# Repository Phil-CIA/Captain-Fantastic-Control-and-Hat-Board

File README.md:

# Captain Fantastic Control and HAT Board

Focused hardware repo for the **Captain Fantastic Home Edition** base control board and its companion **HAT board**.

## Scope
Originally, the system was built around two main boards:
- the **matrix board**
- the **control board**

During development, the control section was split into two physical boards:
- the **base control board**
- the **HAT board**

The HAT board is **not** a revision of the control board. It is a companion board that was created when the original control board was split for development work.

> The separate lamp/switch matrix board work lives in the dedicated repo: `Pinball-Sw-Lamp-Matrix-`.

## Repo layout
- `hardware/control-board/` – current base control-board KiCad source for the next redesign pass
- `hardware/control-board/archive/` – older control-board snapshots and backup exports kept for reference
- `hardware/hat-board/` – companion HAT-board KiCad source
- `firmware/control-board/` – clean control-board firmware baseline for this repo
- `docs/` – project status, redesign notes, firmware migration notes, and bring-up checklists

## Current firmware definition draft
- `firmware/control-board/docs/SYSTEM_BEHAVIOR_CONTRACT.md` – working behavior contract for game states, scoring, audio policy, storage budget, diagnostics, and unresolved decisions to lock before code work
- `docs/SYSTEM_BEHAVIOR_CONTRACT.md` – top-level copy of the same contract for quick review/edit from the main docs area
- `docs/SYSTEM_BEHAVIOR_CONTRACT_MATRIX_BOARD.md` – matrix-board companion contract with lockable decisions and iterative question rounds for switch/lamp protocol behavior

## Current status
- New focused repo created on **2026-04-09**
- The current KiCad files uploaded to GitHub for both boards have been merged into this cleaned repo baseline
- A **.96-inch SSD1306-style I2C OLED** has also been added as a troubleshooting display for boot messages and local status during bring-up
- The next PCB change will likely **not** be the last one; the goal is to keep building and developing the hardware while collecting more real-world feedback
- Two redesign blockers are currently tracked:
  1. the **P-channel solenoid-drive section on the base board sees gate-drive conditions above the recommended `Vgs` range when used on the 26 V supply**
  2. the **HAT-board connector did not line up with the base board**, although there is a temporary development workaround

## Next steps
1. build the board for firmware development and, if needed for proof-of-life output checks, feed **both rails from a current-limited 5 V source** rather than the real 26 V supply
2. use `docs/INITIAL_STUFFING_GUIDE.md` and `docs/BENCH_STUFFING_CHECKLIST.md` to decide what to populate now versus later
3. follow the safe bring-up procedure in `docs/FIRST_POWERUP_CHECKLIST.md`
4. proceed with the **single-channel `TPS1H200A-Q1` smart high-side** respin direction using `docs/SOLENOID_DRIVER_SELECTION.md`, `docs/SINGLE_CHANNEL_SOLENOID_LAYOUT.md`, and `docs/SMART_SWITCH_CHANNEL_BLOCK.md` while continuing the clean firmware migration in `firmware/control-board/`

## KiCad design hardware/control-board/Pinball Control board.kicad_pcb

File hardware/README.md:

# Hardware Notes

This folder contains the hardware design files for the Captain Fantastic base control board and its companion HAT board.

## Contents
- `control-board/` – current base control-board KiCad project and related files
- `control-board/archive/` – older control-board snapshots and backup exports kept for reference
- `hat-board/` – companion HAT-board KiCad project

## Guidance
- The HAT board is **not** a revision of the control board; it was created when the original control board was split during development.
- Treat the uploaded KiCad files now stored under `hardware/` as the **authoritative baseline** for the next redesign pass.
- As redesign decisions are made, keep the active source clearly identified and move stale artifacts out of the way.

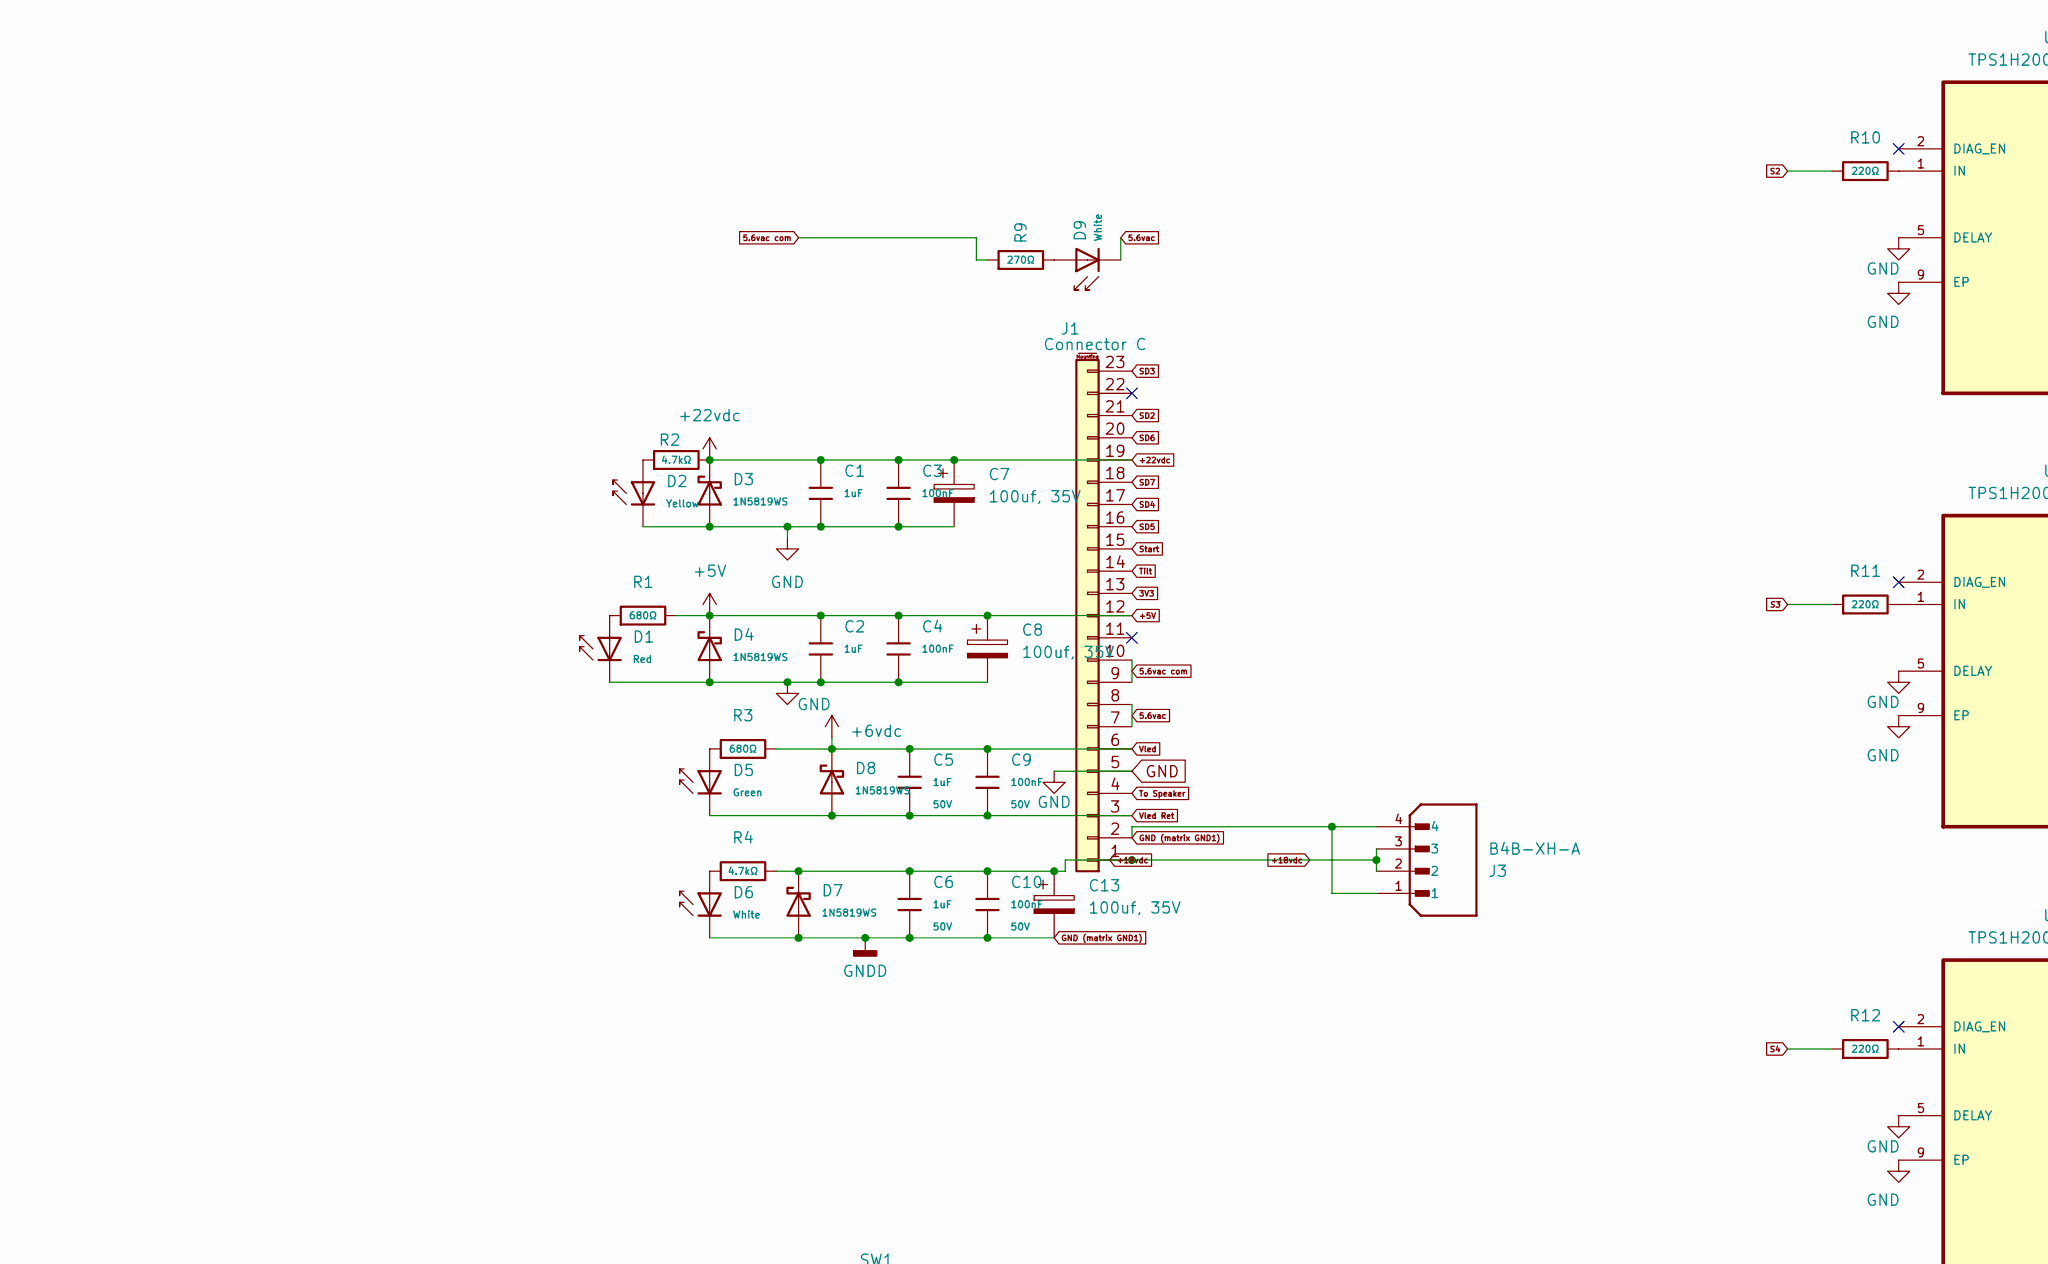
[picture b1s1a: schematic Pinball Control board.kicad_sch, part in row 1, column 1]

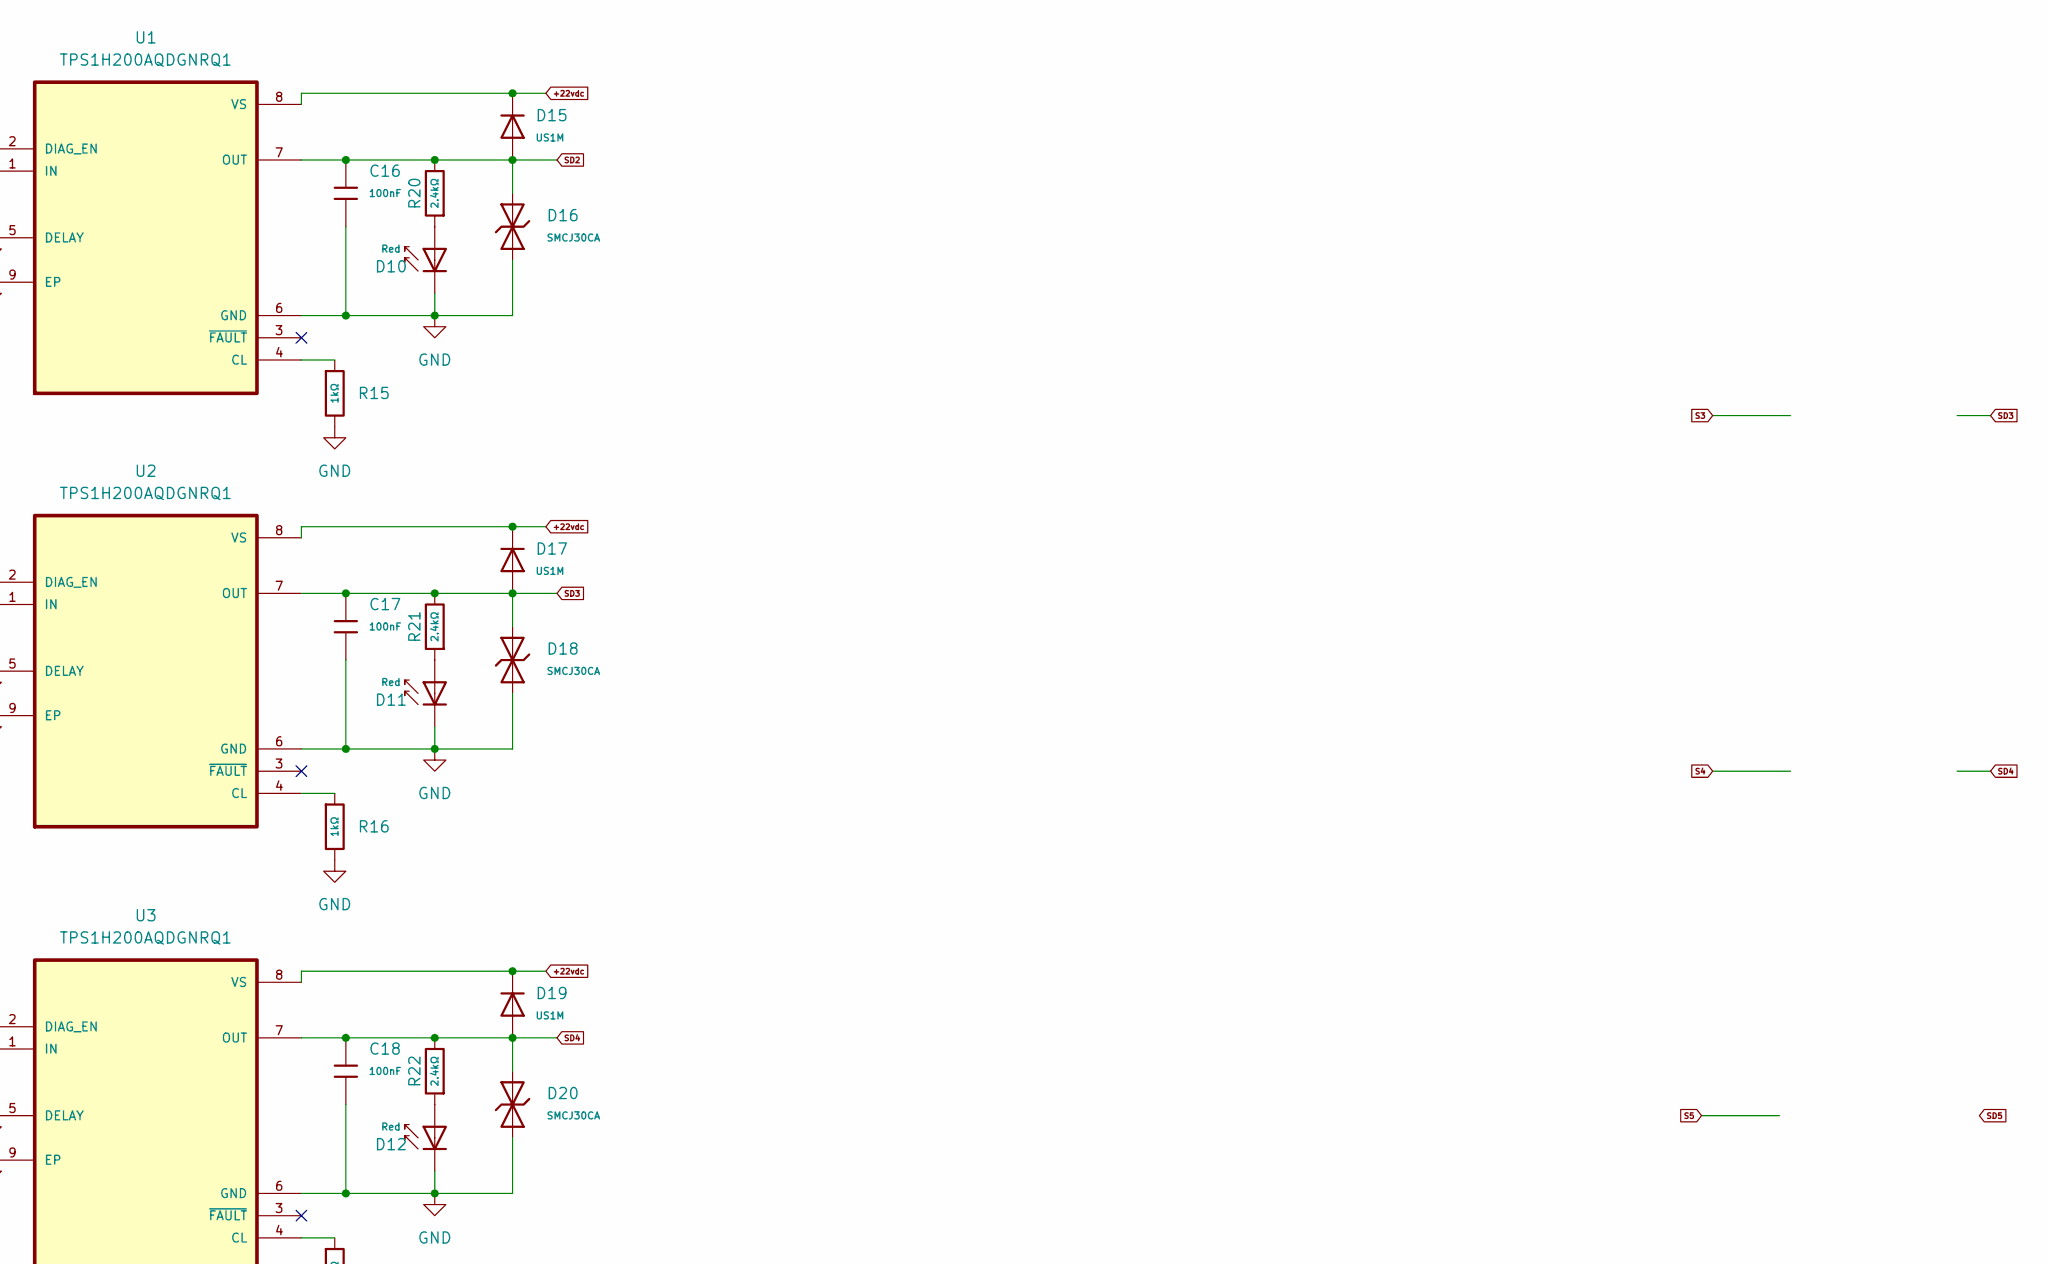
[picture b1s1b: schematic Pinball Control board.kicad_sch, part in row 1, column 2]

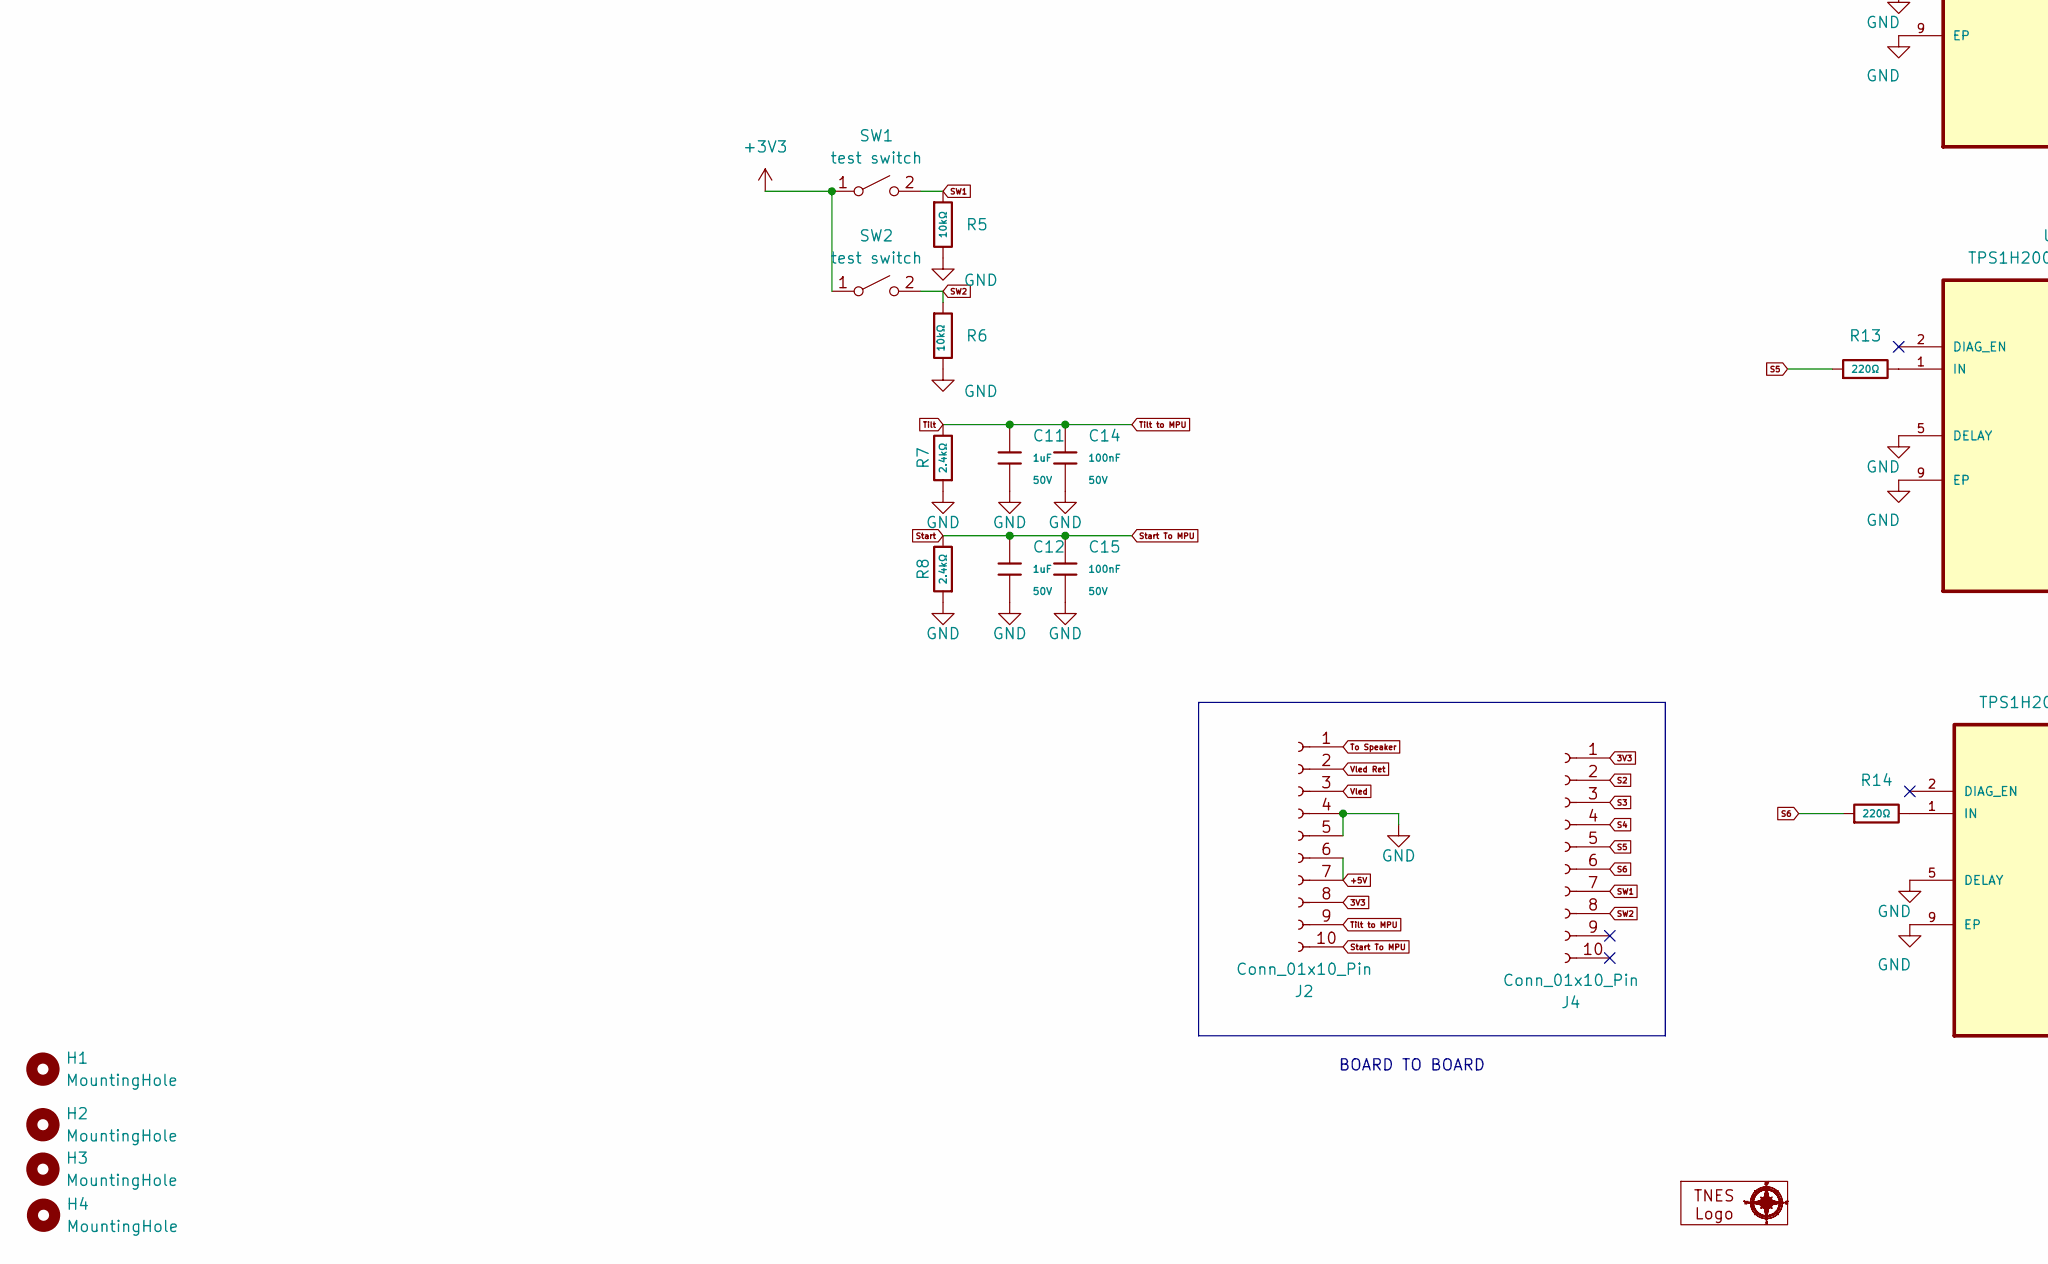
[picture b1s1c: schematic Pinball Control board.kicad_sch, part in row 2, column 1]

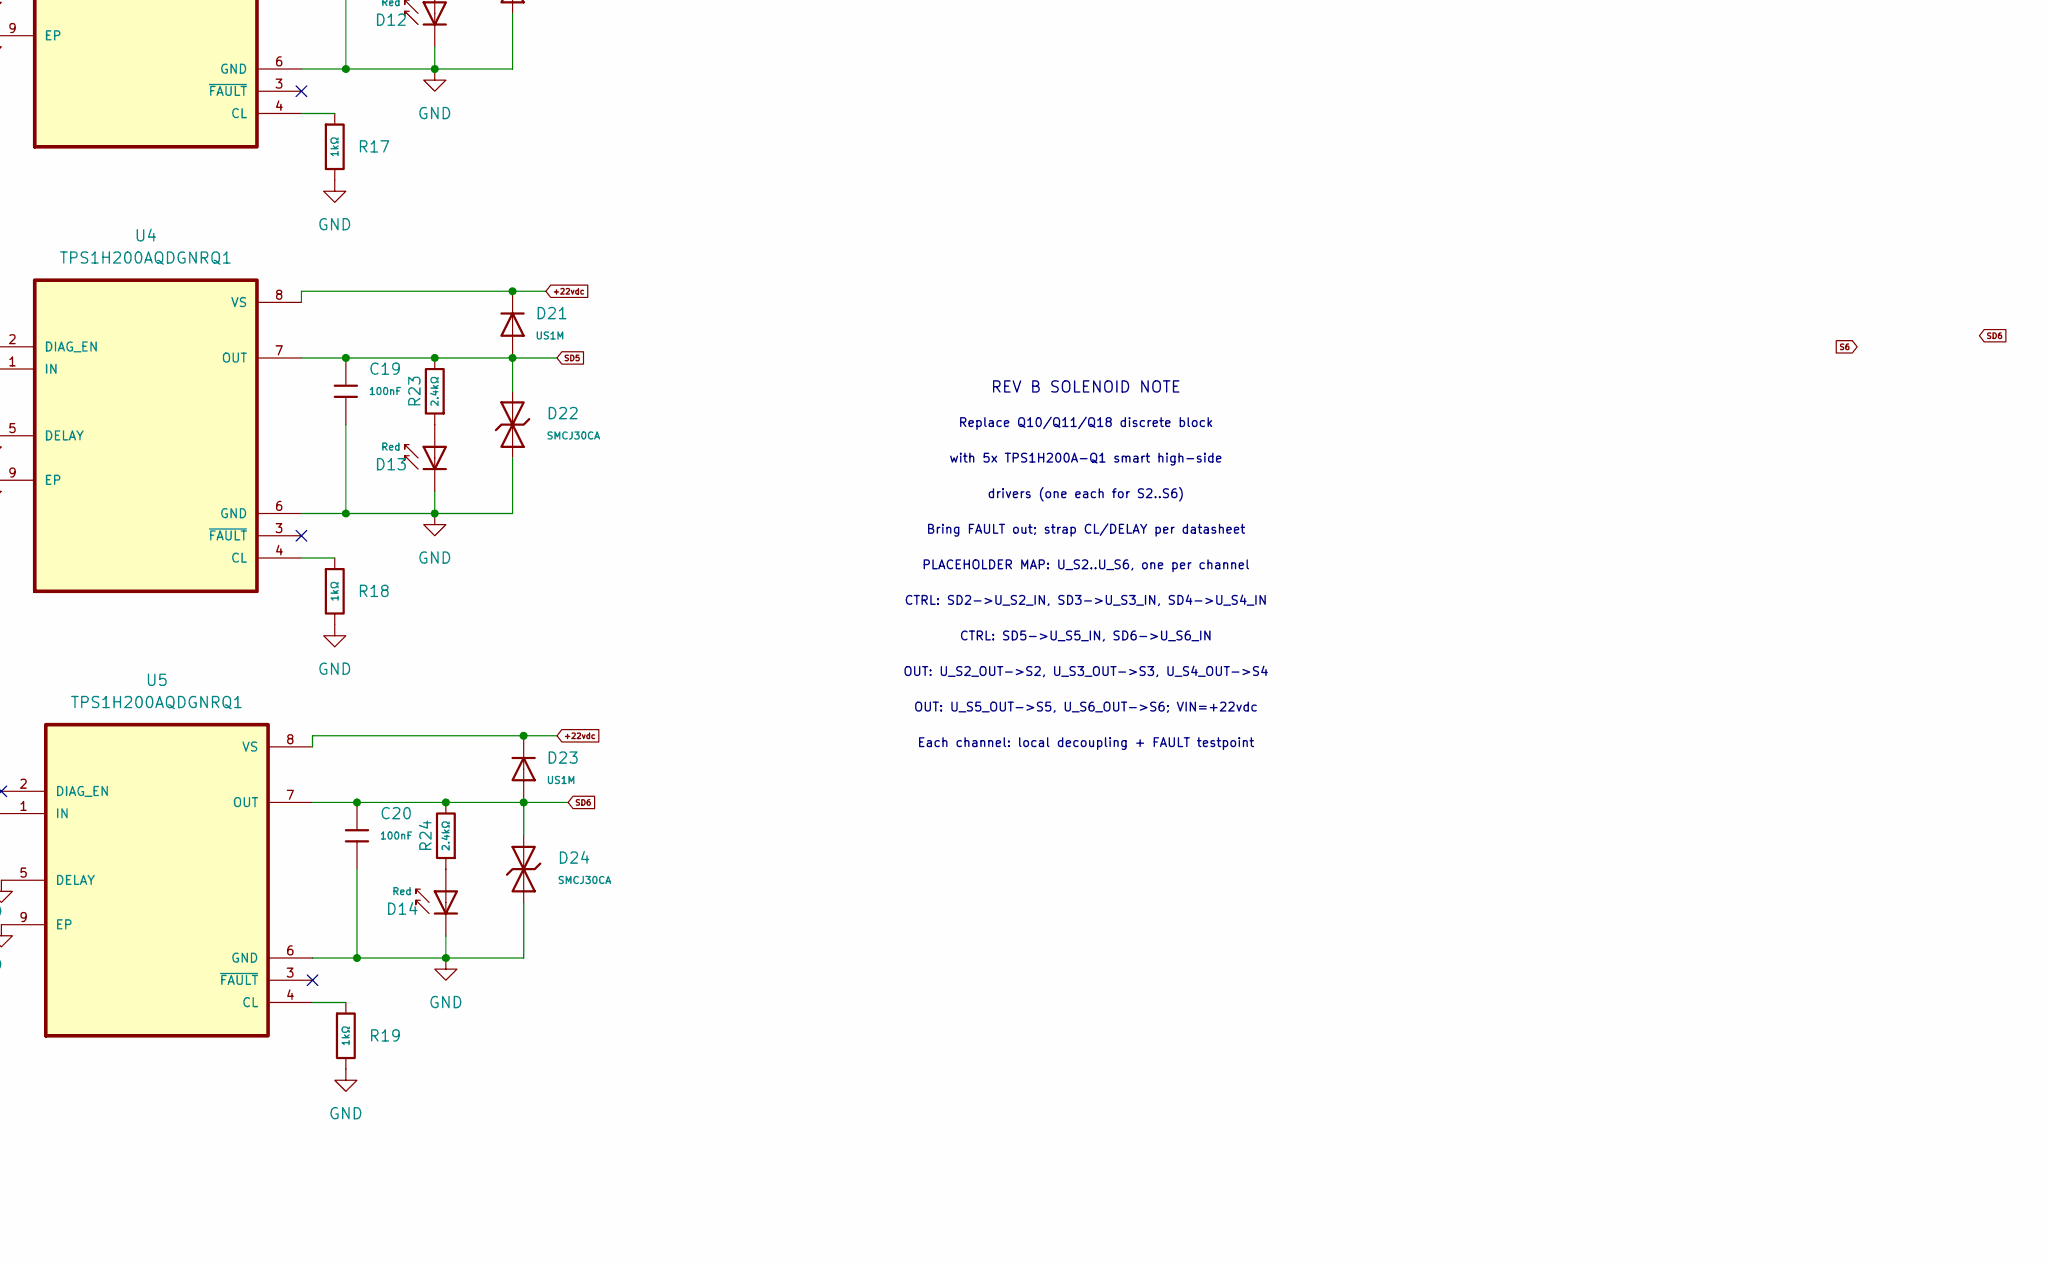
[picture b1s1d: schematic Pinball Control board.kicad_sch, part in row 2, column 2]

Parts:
10mm1: 10mm LOGO
C1, C2, C5, C6, C11, C12: 1uF; C_0805; Voltage Rated 50V; Tolerance ±10%; Part CL21B105KBFNNNE; LCSC C28323
C3, C4, C9, C10, C14, C15, C16, C17, C18, C19, C20: 100nF; C_0805; Voltage Rated 50V; Tolerance ±10%; Part CC0805KRX7R9BB104; LCSC C49678
C7, C8, C13: 100uf, 35V; CP_Radial_D6.3mm_P2.50mm; LCSC C122240
D1, D10, D11, D12, D13, D14: Red; D_0805; Forward Voltage (VF) 1.6V~2.6V; Part NCD0805R1; LCSC C84256
D2: Yellow; D_0805; Part KT-0805Y; LCSC C2296
D3, D4, D7, D8: 1N5819WS; D_SOD-323; Forward Voltage (Vf@If) 600mV@1A; Reverse Voltage (Vr) 40V; Part 1N5819WS; LCSC C191023
D5: Green; D_0805; Part KT-0805G; LCSC C2297
D6, D9: White; D_0805; Part KT-0805W; LCSC C34499
D15, D17, D19, D21, D23: US1M; D_SMA; Forward Voltage (Vf@If) 1.65V@1A; Reverse Voltage (Vr) 1kV; Part US1M; LCSC C412437
D16, D18, D20, D22, D24: SMCJ30CA; D_SMC; Part SMCJ30CA; LCSC C19077607
H1, H2, H3, H4: MountingHole; MountingHole_3.5mm_Pad
J1: Connector C; CONN_SDA-41792_M450_23_MOL
J2, J4: Conn_01x10_Pin; PinHeader_1x10_P2.54mm_Vertical
J3: B4B-XH-A; JST_EH_B4B-EH-A_1x04_P2.50mm_Vertical; PARTREV 7/4/21
R1, R3: 680Ω; R_0805; Overload Voltage (Max) 150V; Tolerance ±1%; Part 0805W8F6800T5E; LCSC C17798
R2, R4: 4.7kΩ; R_0805; Overload Voltage (Max) 150V; Tolerance ±1%; Part 0805W8F4701T5E; LCSC C17673
R5, R6: 10kΩ; R_0805; Overload Voltage (Max) 150V; Tolerance ±1%; Part 0805W8F1002T5E; LCSC C17414
R7, R8, R20, R21, R22, R23, R24: 2.4kΩ; R_0805; Overload Voltage (Max) 150V; Tolerance ±1%; Part 0805W8F2401T5E; LCSC C17526
R9: 270Ω; R_0805; Overload Voltage (Max) 150V; Tolerance ±1%; Part 0805W8F2700T5E; LCSC C17590
R10, R11, R12, R13, R14: 220Ω; R_0805; Overload Voltage (Max) 150V; Tolerance ±1%; Part 0805W8F2200T5E; LCSC C17557
R15, R16, R17, R18, R19: 1kΩ; R_0805; Overload Voltage (Max) 150V; Tolerance ±1%; Part 0805W8F1001T5E; LCSC C17513
SW1, SW2: test switch; Slide Sw LCSC#C7498220; LCSC C7498220
U1, U2, U3, U4, U5: TPS1H200AQDGNRQ1; SOP65P490X110-9N

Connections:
3V3: J1.13, J2.8, J4.1
5.6vac: D9.1, J1.7, J1.8
5.6vac com: J1.9, J1.10, R9.1
+3V3: SW1.1 (A), SW2.1 (A)
+5V: C2.1, C4.1, C8.1, D4.1, J1.12, J2.6, J2.7, R1.2
+18vdc: C6.1, C10.1, C13.1, D7.1, J1.1, J3.2, J3.3, R4.2
+22vdc: C1.1, C3.1, C7.1, D3.1, D15.1, D17.1, D19.1, D21.1, D23.1, J1.19, R2.2, U1.8 (VS), U2.8 (VS), U3.8 (VS), U4.8 (VS), U5.8 (VS)
GND: C1.2, C2.2, C3.2, C4.2, C7.2, C8.2, C11.2, C12.2, C14.2, C15.2, C16.2, C17.2, C18.2, C19.2, C20.2, D1.1, D2.1, D3.2, D4.2, D10.1, D11.1, D12.1, D13.1, D14.1, D16.1, D18.1, D20.1, D22.1, D24.1, J1.5, J2.4, J2.5, R5.2, R6.2, R7.1, R8.1, R15.2, R16.2, R17.2, R18.2, R19.2, U1.5 (DELAY), U1.6 (GND), U1.9 (EP), U2.5 (DELAY), U2.6 (GND), U2.9 (EP), U3.5 (DELAY), U3.6 (GND), U3.9 (EP), U4.5 (DELAY), U4.6 (GND), U4.9 (EP), U5.5 (DELAY), U5.6 (GND), U5.9 (EP)
GND (matrix GND1): C6.2, C10.2, C13.2, D6.1, D7.2, J1.2, J3.1, J3.4
unnamed: D1.2, R1.1
unnamed: D2.2, R2.1
unnamed: D5.2, R3.1
unnamed: D6.2, R4.1
unnamed: D9.2, R9.2
unnamed: D10.2, R20.1
unnamed: D11.2, R21.1
unnamed: D12.2, R22.1
unnamed: D13.2, R23.1
unnamed: D14.2, R24.1
unnamed: R15.1, U1.4 (CL)
unnamed: R10.2, U1.1 (IN)
unnamed: R16.1, U2.4 (CL)
unnamed: R11.2, U2.1 (IN)
unnamed: R17.1, U3.4 (CL)
unnamed: R12.2, U3.1 (IN)
unnamed: R18.1, U4.4 (CL)
unnamed: R13.2, U4.1 (IN)
unnamed: R19.1, U5.4 (CL)
unnamed: R14.2, U5.1 (IN)
S2: J4.2, R10.1
S3: J4.3, R11.1
S4: J4.4, R12.1
S5: J4.5, R13.1
S6: J4.6, R14.1
SD2: C16.1, D15.2, D16.2, J1.21, R20.2, U1.7 (OUT)
SD3: C17.1, D17.2, D18.2, J1.23, R21.2, U2.7 (OUT)
SD4: C18.1, D19.2, D20.2, J1.17, R22.2, U3.7 (OUT)
SD5: C19.1, D21.2, D22.2, J1.16, R23.2, U4.7 (OUT)
SD6: C20.1, D23.2, D24.2, J1.20, R24.2, U5.7 (OUT)
SD7: J1.18
SW1: J4.7, R5.1, SW1.2 (B)
SW2: J4.8, R6.1, SW2.2 (B)
Start: C12.1, C15.1, J1.15, J2.10, R8.2
Tilt: C11.1, C14.1, J1.14, J2.9, R7.2
To Speaker: J1.4, J2.1
Vled: C5.1, C9.1, D8.1, J1.6, J2.3, R3.2
Vled Ret: C5.2, C9.2, D5.1, D8.2, J1.3, J2.2

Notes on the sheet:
REV B SOLENOID NOTE
OUT: U_S2_OUT->S2, U_S3_OUT->S3, U_S4_OUT->S4
drivers (one each for S2..S6)
with 5x TPS1H200A-Q1 smart high-side
Bring FAULT out; strap CL/DELAY per datasheet
CTRL: SD5->U_S5_IN, SD6->U_S6_IN
Each channel: local decoupling + FAULT testpoint
PLACEHOLDER MAP: U_S2..U_S6, one per channel
OUT: U_S5_OUT->S5, U_S6_OUT->S6; VIN=+22vdc
Replace Q10/Q11/Q18 discrete block
BOARD TO BOARD
CTRL: SD2->U_S2_IN, SD3->U_S3_IN, SD4->U_S4_IN

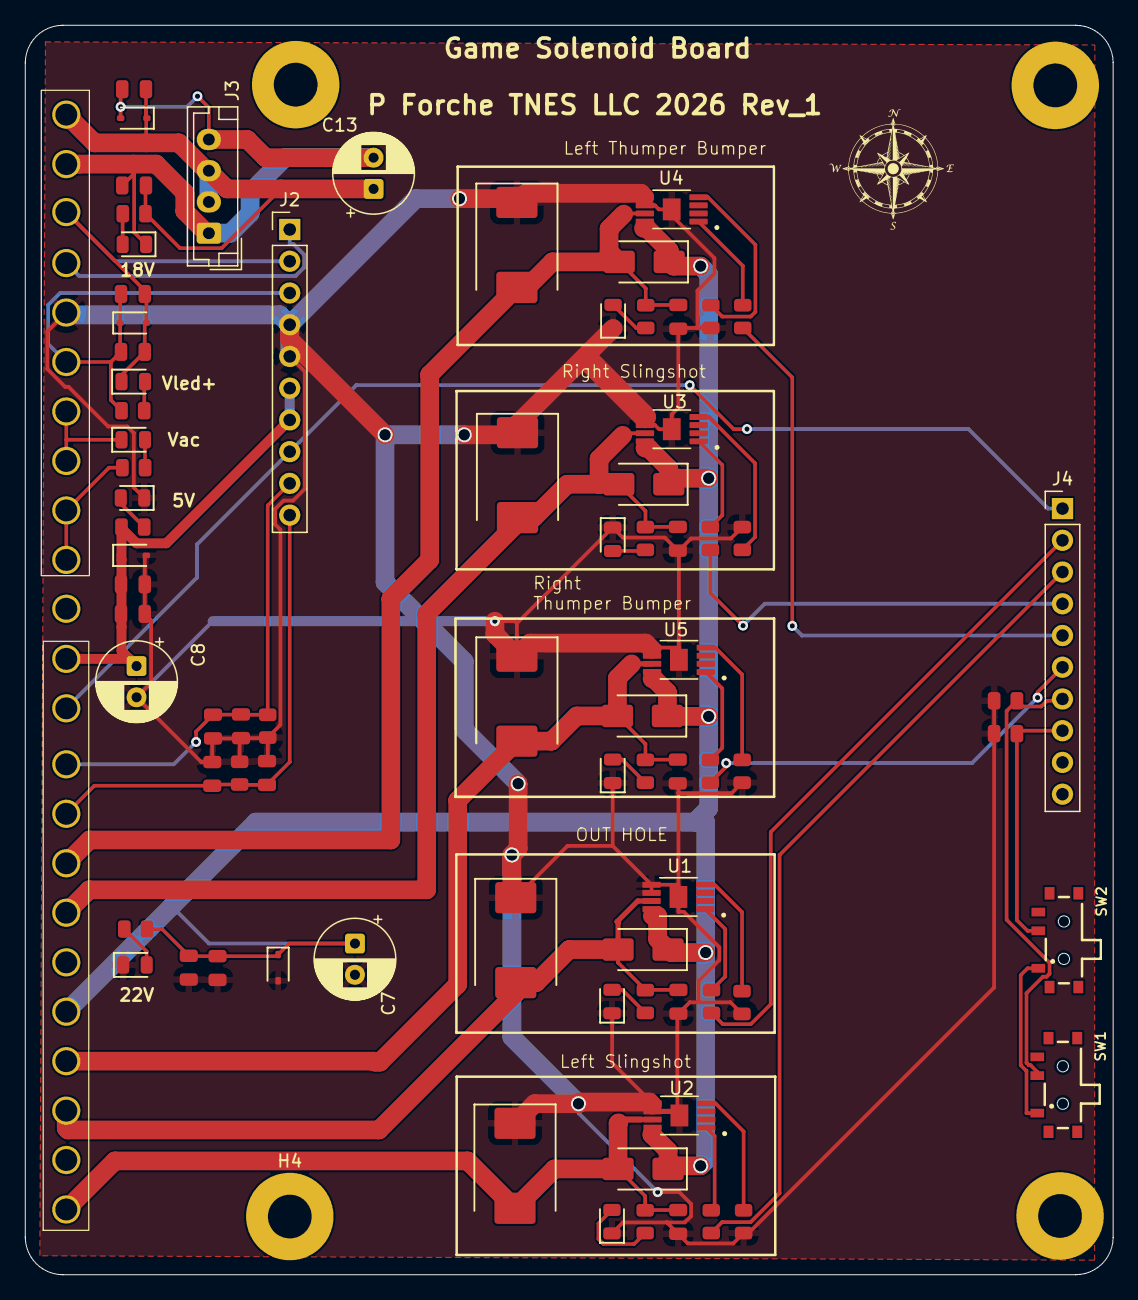
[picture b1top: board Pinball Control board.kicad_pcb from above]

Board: 2 copper layers, 87.1 x 100.0 mm, 84 parts (0 on the bottom side), 46 nets.
